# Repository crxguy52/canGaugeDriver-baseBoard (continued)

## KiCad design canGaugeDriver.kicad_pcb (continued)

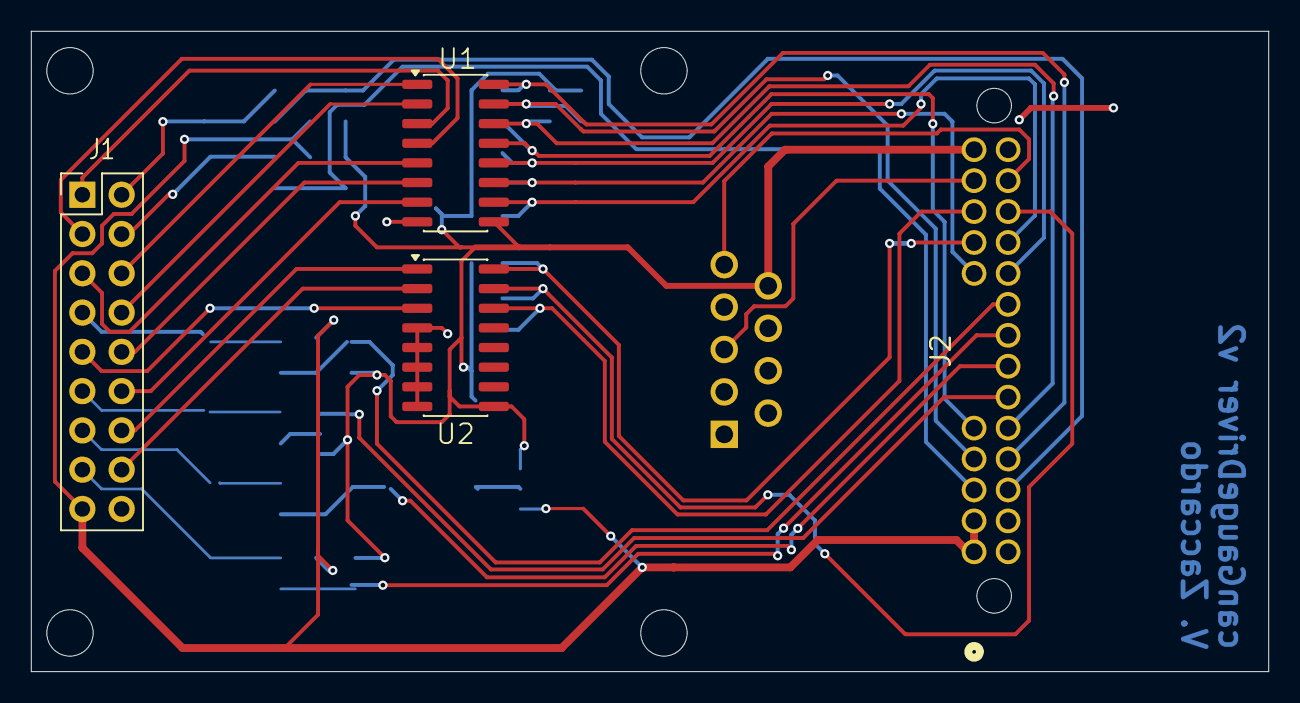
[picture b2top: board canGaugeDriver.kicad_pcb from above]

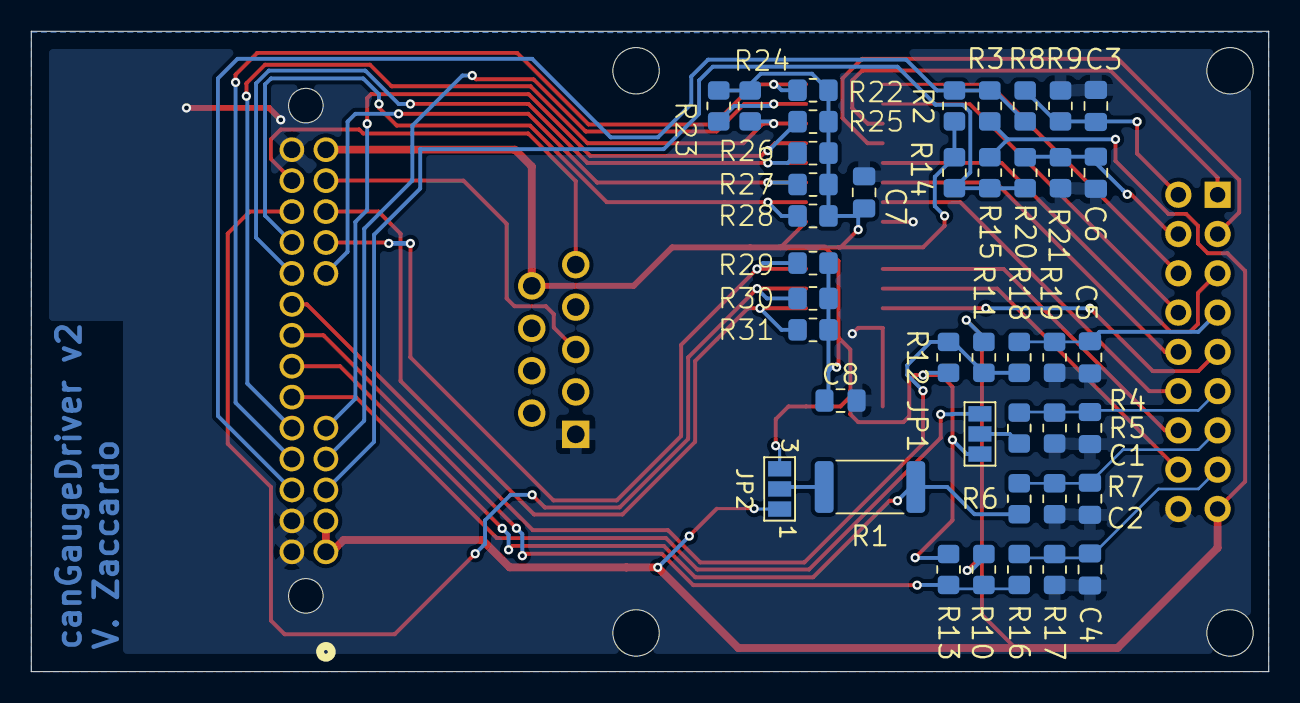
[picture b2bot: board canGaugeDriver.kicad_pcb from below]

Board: 2 copper layers, 80.0 x 41.4 mm, 50 parts (41 on the bottom side), 39 nets.
